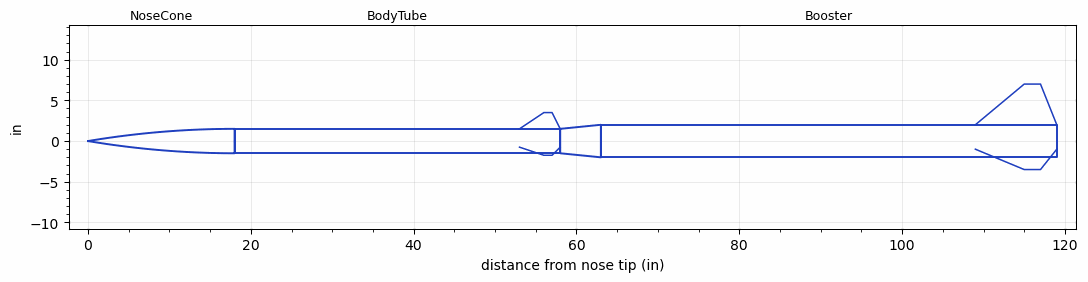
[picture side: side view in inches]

<RASAeroDocument>
 <FileVersion>2</FileVersion>
 <RocketDesign>
  <NoseCone>
   <Length>18</Length>
   <Diameter>3</Diameter>
   <Shape>Tangent Ogive</Shape>
   <Location>0</Location>
  </NoseCone>
  <BodyTube>
   <Length>40</Length>
   <Diameter>3</Diameter>
   <Location>18</Location>
   <Fin>
    <Count>3</Count>
    <Chord>5</Chord>
    <Span>2</Span>
    <SweepDistance>3</SweepDistance>
    <TipChord>1</TipChord>
    <Thickness>0.25</Thickness>
    <LERadius>0.125</LERadius>
    <Location>5</Location>
    <AirfoilSection>Double Wedge</AirfoilSection>
    <FX1>1</FX1>
    <FX3>1</FX3>
   </Fin>
  </BodyTube>
  <Booster>
   <Length>56</Length>
   <Diameter>4</Diameter>
   <InsideDiameter>3</InsideDiameter>
   <Location>58</Location>
   <ShoulderLength>5</ShoulderLength>
   <Fin>
    <Count>3</Count>
    <Chord>10</Chord>
    <Span>5</Span>
    <SweepDistance>6</SweepDistance>
    <TipChord>2</TipChord>
    <Thickness>0.25</Thickness>
    <LERadius>0.125</LERadius>
    <Location>10</Location>
    <AirfoilSection>Double Wedge</AirfoilSection>
    <FX1>1</FX1>
    <FX3>1</FX3>
   </Fin>
  </Booster>
  <Surface>Smooth (Zero Roughness)</Surface>
  <ModifiedBarrowman>False</ModifiedBarrowman>
  <Turbulence>False</Turbulence>
  <UseBooster1>False</UseBooster1>
  <UseBooster2>False</UseBooster2>
 </RocketDesign>
 <LaunchSite>
  <Altitude>5000</Altitude>
  <Pressure>0</Pressure>
  <RodAngle>0</RodAngle>
  <RodLength>4</RodLength>
  <Temperature>95</Temperature>
  <WindSpeed>0</WindSpeed>
 </LaunchSite>
 <Recovery>
  <Altitude1>1000</Altitude1>
  <Altitude2>1000</Altitude2>
  <DeviceType1>None</DeviceType1>
  <DeviceType2>None</DeviceType2>
  <Event1>False</Event1>
  <Event2>False</Event2>
  <Size1>1</Size1>
  <Size2>1</Size2>
  <EventType1>None</EventType1>
  <EventType2>None</EventType2>
  <CD1>1.33</CD1>
  <CD2>1.33</CD2>
 </Recovery>
 <SimulationList>
  <Simulation>
   <SustainerEngine>1/2A2  (AP)</SustainerEngine>
   <SustainerLaunchWt>17</SustainerLaunchWt>
   <SustainerCG>27</SustainerCG>
   <SustainerIgnitionDelay>0</SustainerIgnitionDelay>
   <Booster1Engine>N2900-CL  (CTI)</Booster1Engine>
   <Booster1LaunchWt>57</Booster1LaunchWt>
   <Booster1SeparationDelay>0</Booster1SeparationDelay>
   <Booster1IgnitionDelay>0</Booster1IgnitionDelay>
   <Booster1CG>68</Booster1CG>
   <Booster1NozzleDiameter>1</Booster1NozzleDiameter>
   <IncludeBooster1>True</IncludeBooster1>
   <Booster2Delay>0</Booster2Delay>
   <IncludeBooster2>False</IncludeBooster2>
   <TimetoApogee>48.97889</TimetoApogee>
   <MaxAltitude>41885.03</MaxAltitude>
   <MaxVelocity>2092.428</MaxVelocity>
  </Simulation>
 </SimulationList>
</RASAeroDocument>
